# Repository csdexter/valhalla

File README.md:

# Valhalla

This repository contains version-controlled material related to operation
Valhalla. The documentation counterparts are currently stored in Google Drive.

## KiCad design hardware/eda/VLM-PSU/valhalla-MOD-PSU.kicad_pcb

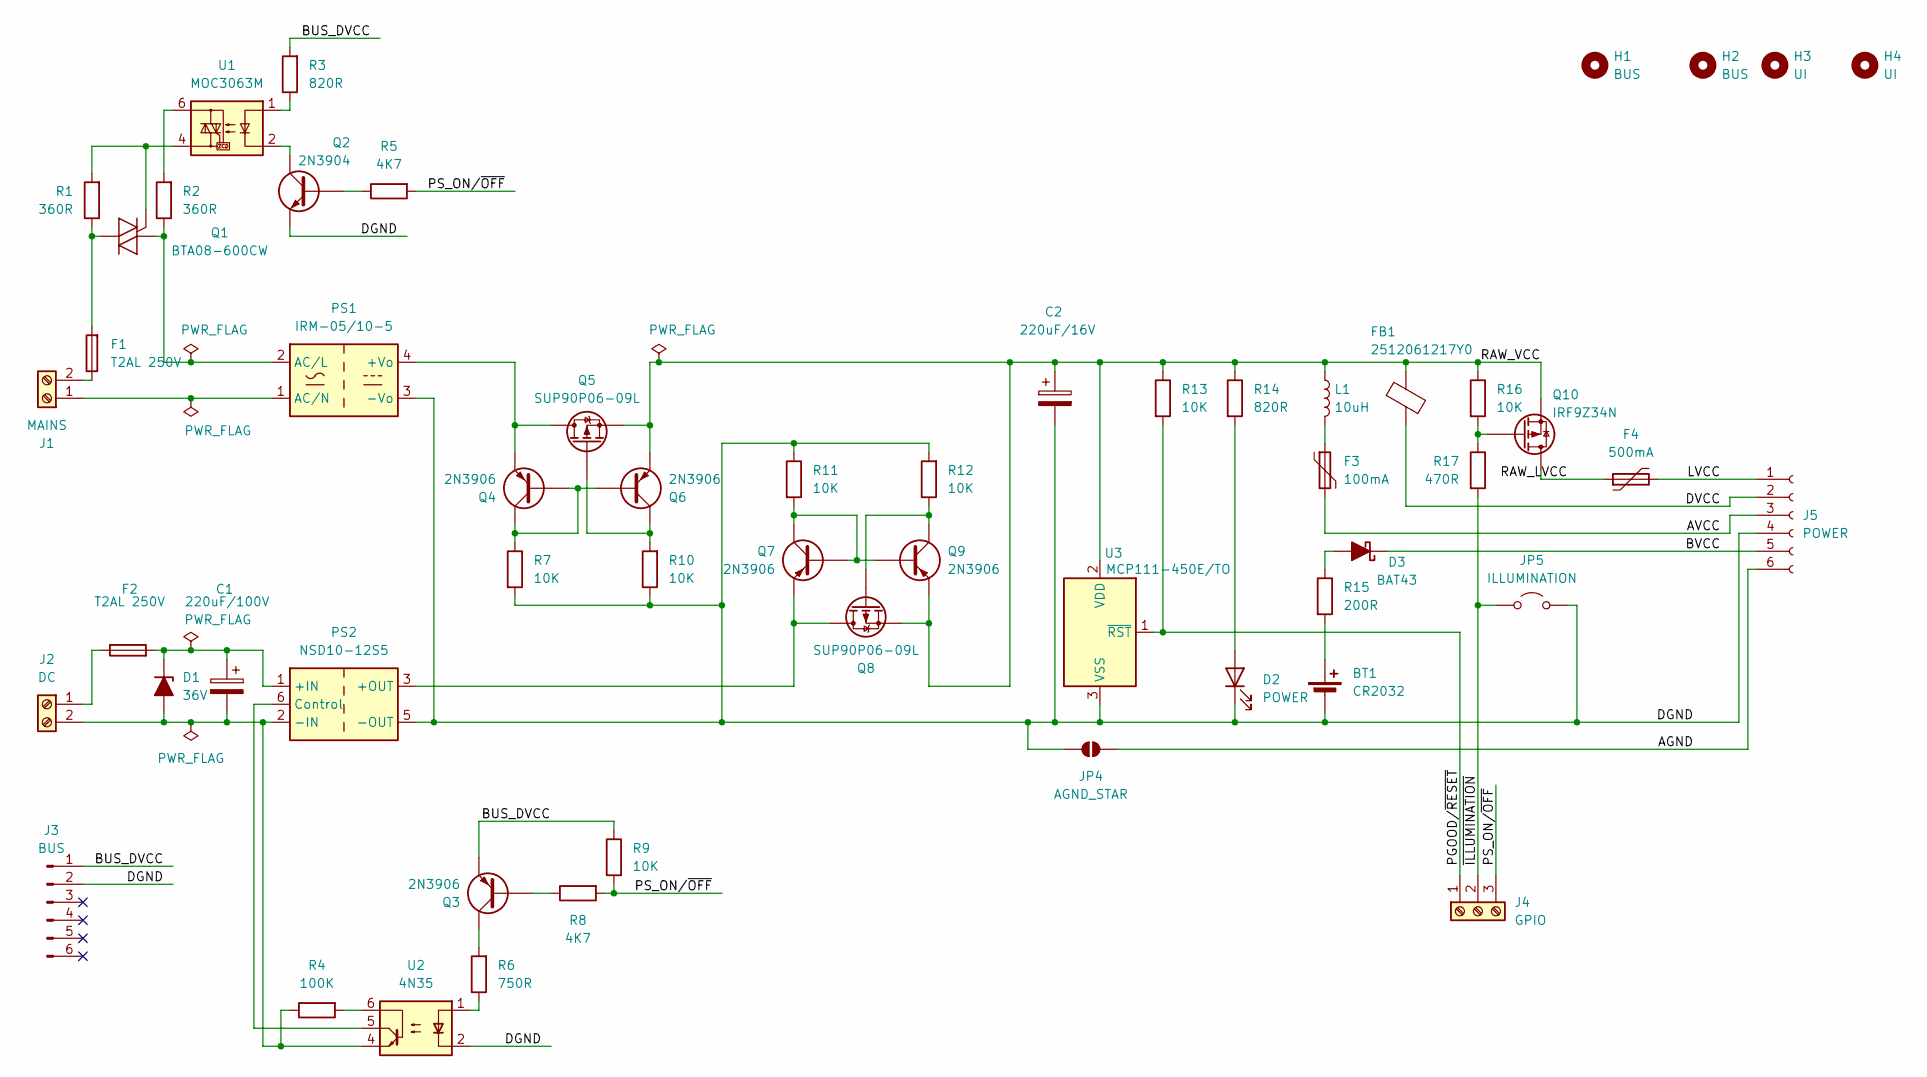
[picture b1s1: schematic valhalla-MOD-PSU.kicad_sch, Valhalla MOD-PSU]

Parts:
BT1: CR2032; BAT-TH_BS-02-A1AJ010
C1: 220uF/100V; CP_Radial_D6.3mm_P2.50mm
C2: 220uF/16V; CP_Radial_D6.3mm_P2.50mm
D1: 36V; D_DO-41_SOD81_P5.08mm_Vertical_KathodeUp
D2: POWER; LED_D3.0mm_Horizontal_O1.27mm_Z2.0mm
D3: BAT43; D_DO-34_SOD68_P5.08mm_Vertical_KathodeUp
F1, F2: T2AL 250V; Fuseholder_Clip-5x20mm_Bel_FC-203-22_Lateral_P17.80x5.00mm_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
F3: 100mA; Fuse_BelFuse_0ZRE0005FF_L8.3mm_W3.8mm
F4: 500mA; Fuse_BelFuse_0ZRE0005FF_L8.3mm_W3.8mm
FB1: 2512061217Y0; L_Axial_L5.0mm_D3.6mm_P10.00mm_Horizontal_Murata_BL01RN1A2A2
H1, H2: BUS; MountingHole_3.2mm_M3_ISO7380
H3, H4: UI; MountingHole_3.2mm_M3_ISO7380
J1: MAINS; TerminalBlock_Phoenix_MKDS-3-2-5.08_1x02_P5.08mm_Horizontal
J2: DC; TerminalBlock_Phoenix_MKDS-3-2-5.08_1x02_P5.08mm_Horizontal
J3: BUS; Molex_KK-254_A-7478-06A_1x06_P2.54mm_Horizontal
J4: GPIO; TerminalBlock_Phoenix_MPT-0,5-3-2.54_1x03_P2.54mm_Horizontal
J5: POWER; CONN-TN_39301060
JP4: AGND_STAR; SolderJumper-2_P1.3mm_Open_RoundedPad1.0x1.5mm
JP5: ILLUMINATION; PinHeader_1x02_P2.54mm_Vertical
L1: 10uH; L_Radial_D8.7mm_P5.00mm_Fastron_07HCP
PS1: IRM-05/10-5; Converter_ACDC_MeanWell_IRM-05-xx_THT
PS2: NSD10-12S5; Converter_DCDC_MeanWell_NSD10_THT
Q1: BTA08-600CW; TO-220-3_Horizontal_TabDown
Q2: 2N3904; TO-92_Wide
Q3, Q4, Q6, Q7, Q9: 2N3906; TO-92_Wide
Q5, Q8: SUP90P06-09L; TO-220-3_Horizontal_TabDown
Q10: IRF9Z34N; TO-220-3_Horizontal_TabDown
R1, R2: 360R; R_Axial_DIN0207_L6.3mm_D2.5mm_P5.08mm_Vertical
R3, R14: 820R; R_Axial_DIN0207_L6.3mm_D2.5mm_P5.08mm_Vertical
R4: 100K; R_Axial_DIN0207_L6.3mm_D2.5mm_P5.08mm_Vertical
R5, R8: 4K7; R_Axial_DIN0207_L6.3mm_D2.5mm_P5.08mm_Vertical
R6: 750R; R_Axial_DIN0207_L6.3mm_D2.5mm_P5.08mm_Vertical
R7, R9, R10, R11, R12, R13, R16: 10K; R_Axial_DIN0207_L6.3mm_D2.5mm_P5.08mm_Vertical
R15: 200R; R_Axial_DIN0207_L6.3mm_D2.5mm_P5.08mm_Vertical
R17: 470R; R_Axial_DIN0207_L6.3mm_D2.5mm_P5.08mm_Vertical
U1: MOC3063M; DIP-6_W10.16mm
U2: 4N35; DIP-6_W7.62mm
U3: MCP111-450E/TO; TO-92_Wide

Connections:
/AGND: J5.6, JP4.2 (B)
/AVCC: F3.2, J5.3
/BUS_DVCC: J3.1, Q3.1 (E), R3.2, R9.1
/BVCC: D3.1 (K), J5.5
/DGND: BT1.2 (-), C2.2, D2.1 (K), J3.2, J5.4, JP4.1 (A), JP5.2 (B), PS1.3 (-Vo), PS2.5 (-OUT), Q2.1 (E), R7.2, R10.1, R11.1, R12.2, U2.2, U3.3 (VSS)
/DVCC: FB1.2, J5.2
/LVCC: F4.2, J5.1
/PGOOD/~RESET: J4.1, R13.2, U3.1 (~RST)
/PS_ON/~OFF: J4.3, R5.2, R8.2, R9.2
/RAW_LVCC: F4.1, Q10.2 (D)
/RAW_VCC: C2.1, FB1.1, L1.1, Q5.3 (S), Q6.1 (E), Q8.3 (S), Q9.1 (E), Q10.3 (S), R13.1, R14.1, R16.1, U3.2 (VDD)
/~ILLUMINATION: J4.2, JP5.1 (A), R17.2
unnamed: BT1.1 (+), R15.2
unnamed: C1.2, D1.2 (A), J2.2, PS2.2 (-IN), R4.1, U2.4
unnamed: C1.1, D1.1 (K), F2.2, PS2.1 (+IN)
unnamed: D2.2 (A), R14.2
unnamed: D3.2 (A), R15.1
unnamed: F3.1, L1.2
unnamed: J1.1, PS1.1 (AC/N)
unnamed: F1.1, J1.2
unnamed: F2.1, J2.1
unnamed: PS1.4 (+Vo), Q4.1 (E), Q5.2 (D)
unnamed: PS1.2 (AC/L), Q1.1 (A1), R2.1
unnamed: PS2.3 (+OUT), Q7.1 (E), Q8.2 (D)
unnamed: PS2.6 (Control), U2.5
unnamed: F1.2, Q1.2 (A2), R1.1
unnamed: Q1.3 (G), R1.2, U1.4
unnamed: Q2.2 (B), R5.1
unnamed: Q2.3 (C), U1.2
unnamed: Q3.2 (B), R8.1
unnamed: Q3.3 (C), R6.2
unnamed: Q4.2 (B), Q4.3 (C), Q6.2 (B), R7.1
unnamed: Q5.1 (G), Q6.3 (C), R10.2
unnamed: Q7.2 (B), Q7.3 (C), Q9.2 (B), R11.2
unnamed: Q8.1 (G), Q9.3 (C), R12.1
unnamed: Q10.1 (G), R16.2, R17.1
unnamed: R2.2, U1.6
unnamed: R3.1, U1.1
unnamed: R4.2, U2.6
unnamed: R6.1, U2.1

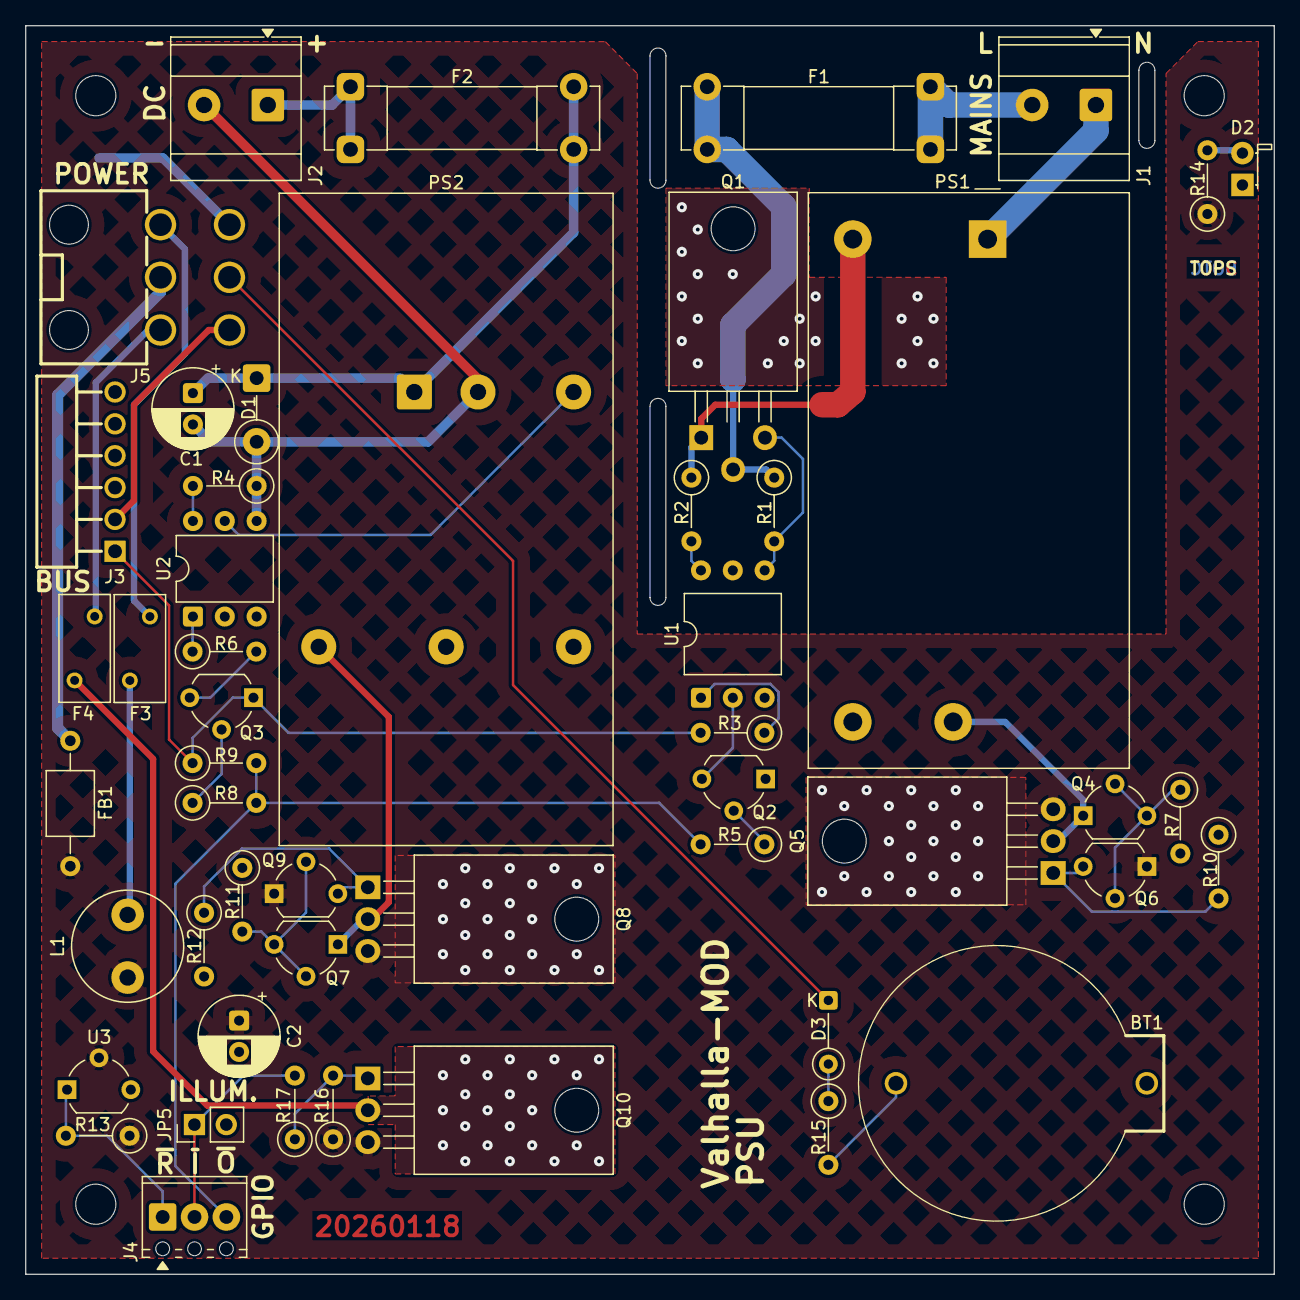
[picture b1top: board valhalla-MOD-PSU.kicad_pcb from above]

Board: 2 copper layers, 99.6 x 99.6 mm, 55 parts (1 on the bottom side), 40 nets.

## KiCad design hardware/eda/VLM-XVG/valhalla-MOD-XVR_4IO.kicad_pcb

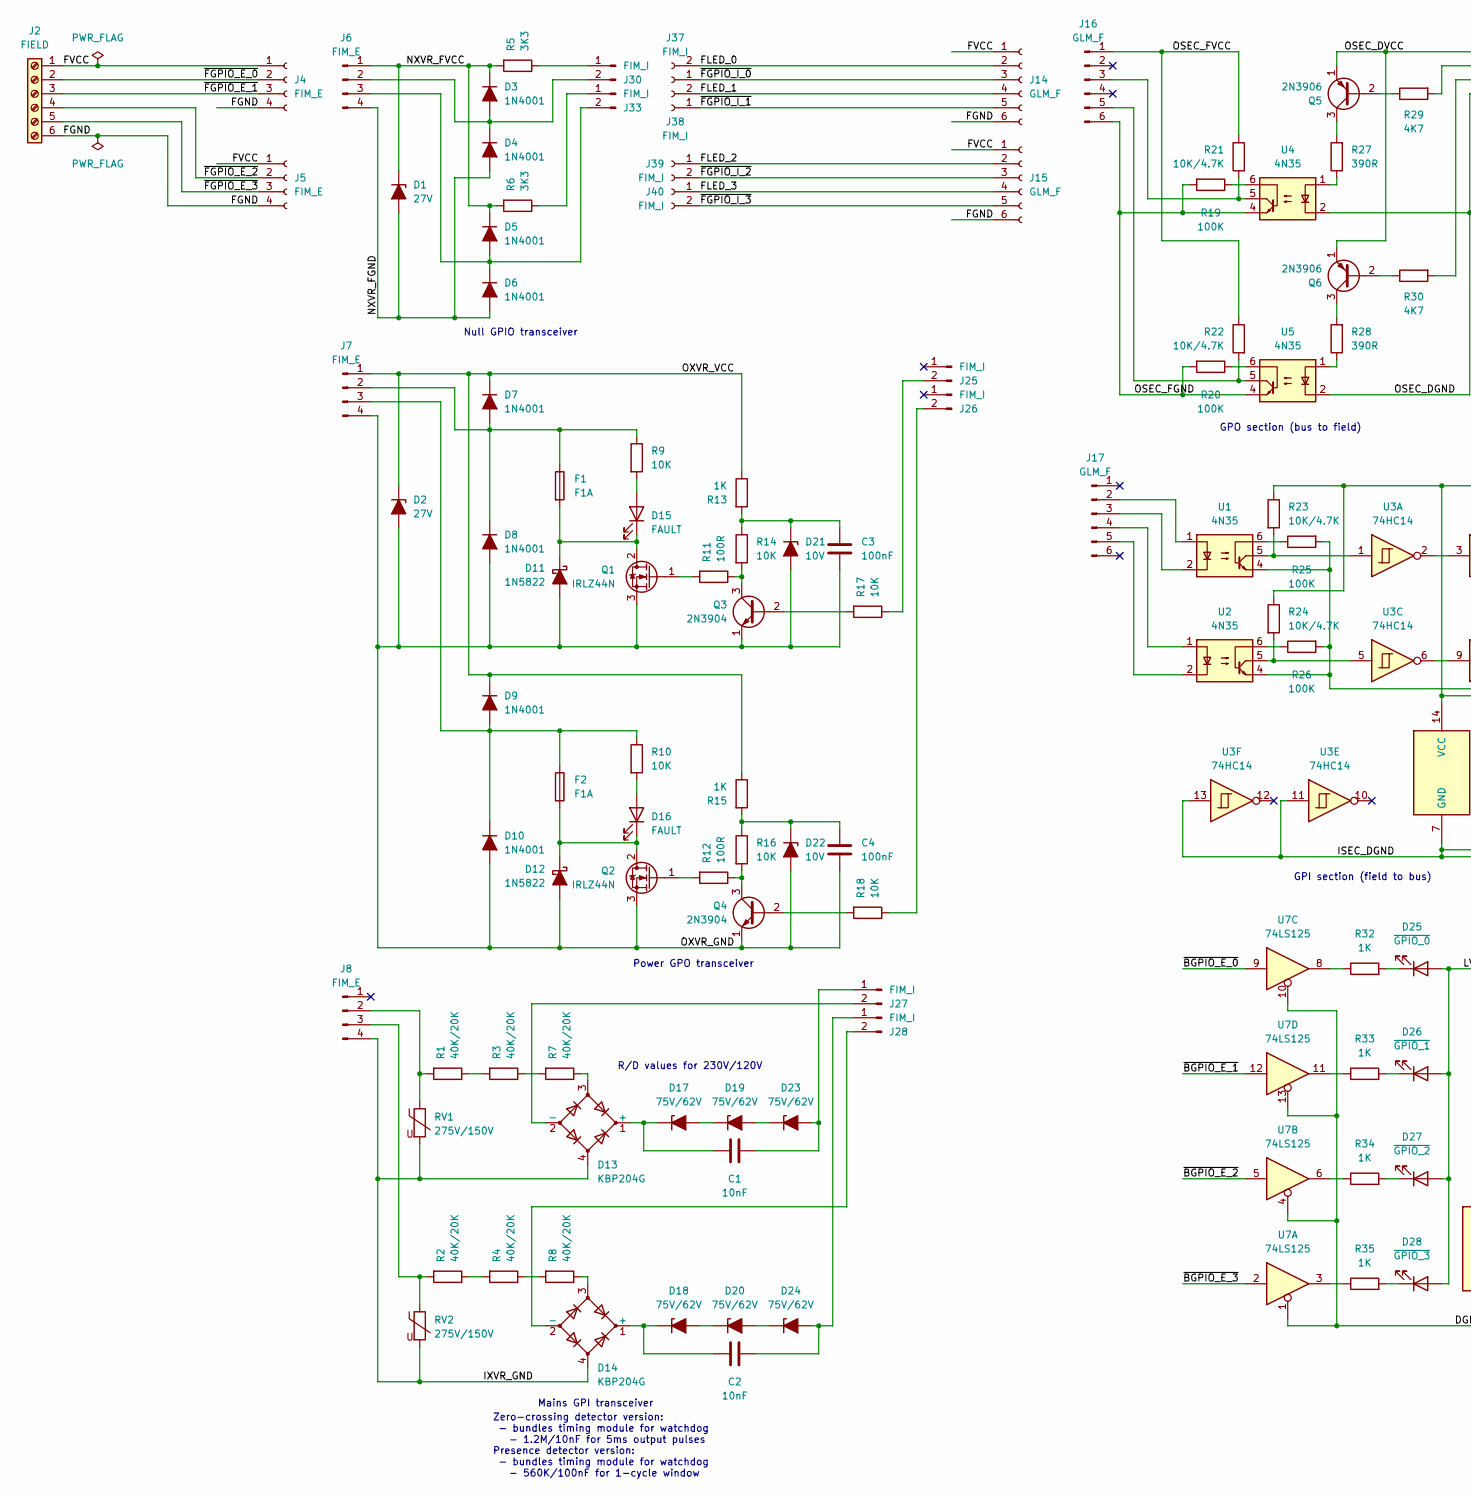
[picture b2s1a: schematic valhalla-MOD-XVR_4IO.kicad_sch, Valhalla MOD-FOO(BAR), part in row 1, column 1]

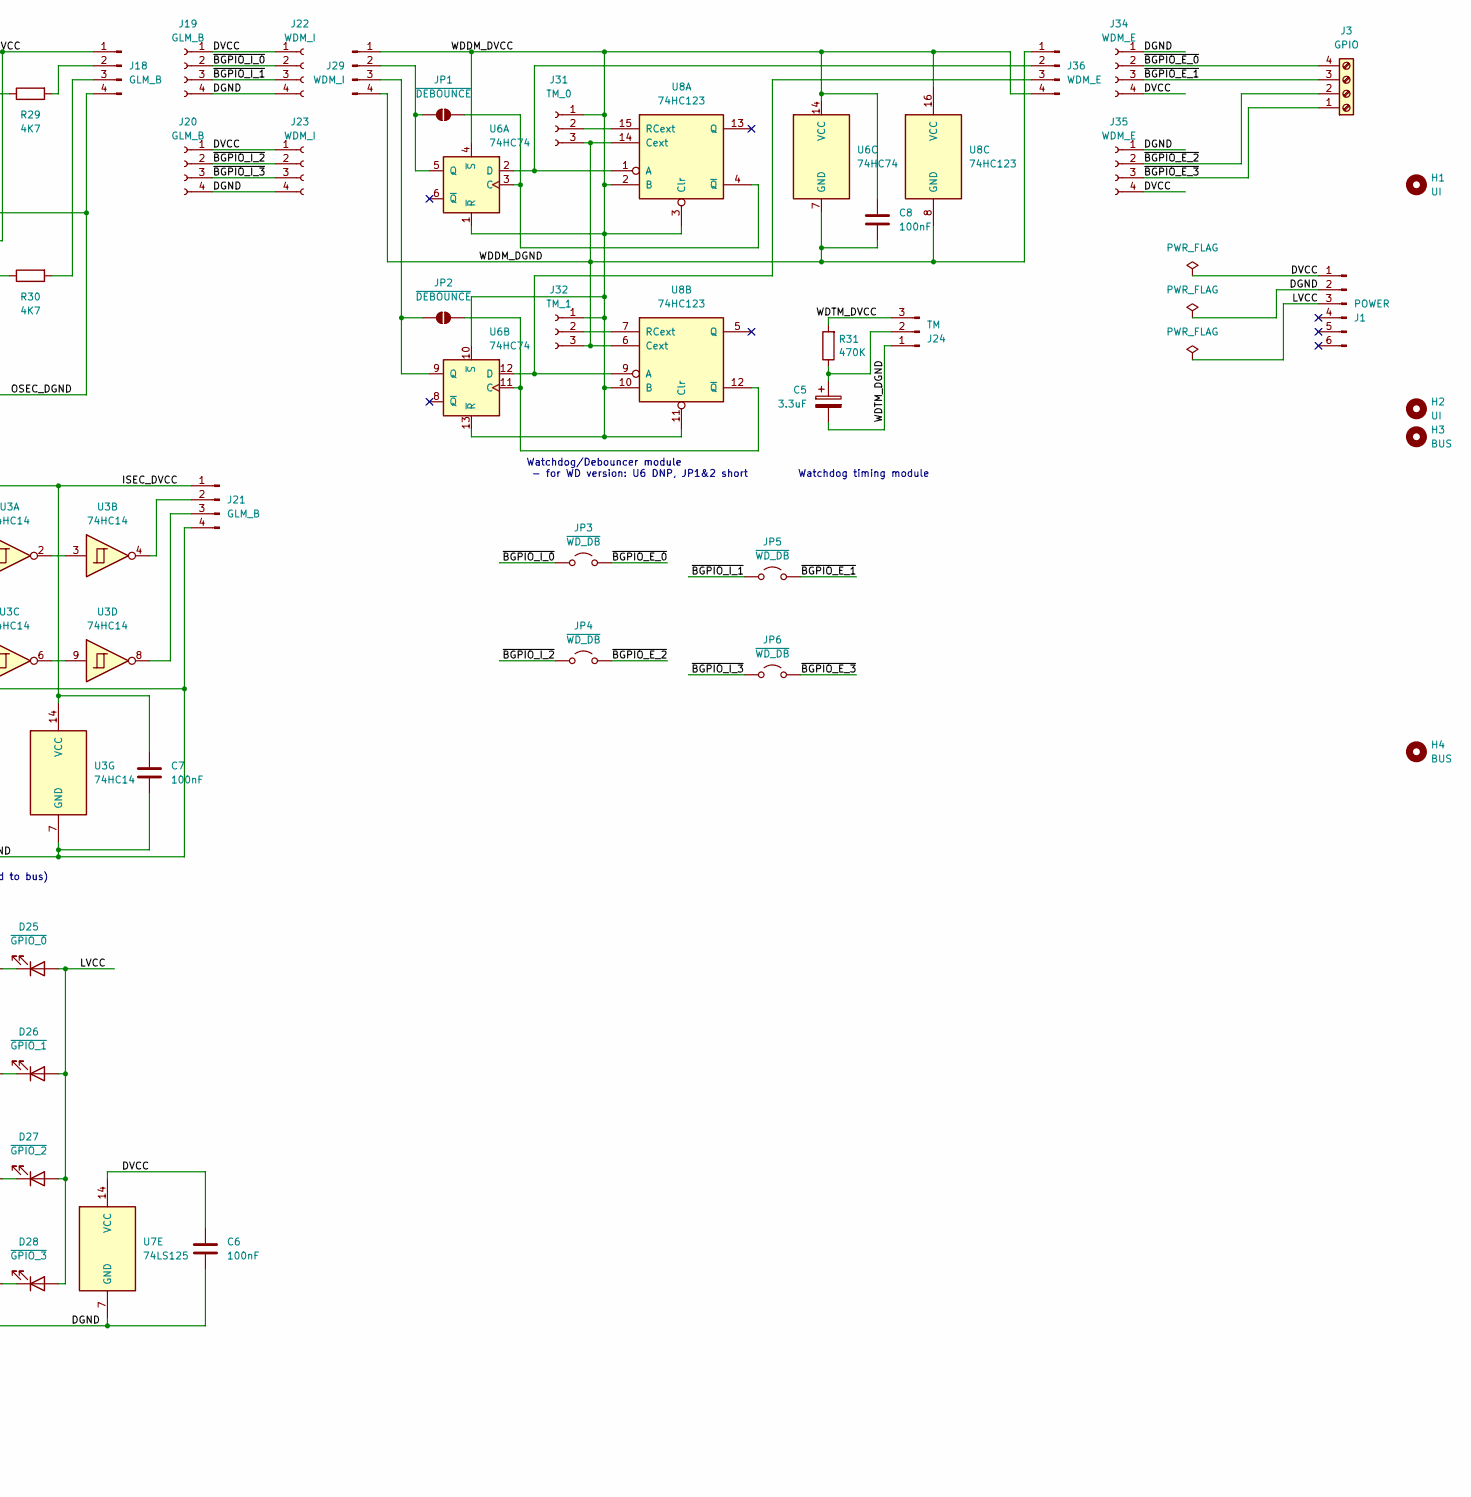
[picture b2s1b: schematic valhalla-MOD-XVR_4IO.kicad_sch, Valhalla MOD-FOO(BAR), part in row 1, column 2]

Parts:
C1, C2: 10nF; C_Disc_D11.0mm_W5.0mm_P7.50mm
C3, C4: 100nF; C_Rect_L7.2mm_W2.5mm_P5.00mm_FKS2_FKP2_MKS2_MKP2
C5: 3.3uF; CP_Radial_D5.0mm_P2.00mm
C6, C7, C8: 100nF; C_Rect_L4.0mm_W2.5mm_P2.50mm
D1, D2: 27V; D_DO-41_SOD81_P5.08mm_Vertical_KathodeUp
D3, D4, D5, D6, D7, D8, D9, D10: 1N4001; D_DO-41_SOD81_P5.08mm_Vertical_KathodeUp
D11, D12: 1N5822; D_DO-201AD_P5.08mm_Vertical_KathodeUp
D13, D14: KBP204G; Diode_Bridge_KBP_14.5x3.5x10.0mm_P3.81mm
D15, D16: FAULT; LED_D3.0mm
D17, D18, D19, D20, D23, D24: 75V/62V; D_DO-41_SOD81_P5.08mm_Vertical_KathodeUp
D21, D22: 10V; D_DO-35_SOD27_P5.08mm_Vertical_KathodeUp
D25: ~{GPIO_0}; LED_D3.0mm_Horizontal_O1.27mm_Z2.0mm
D26: ~{GPIO_1}; LED_D3.0mm_Horizontal_O3.81mm_Z6.0mm
D27: ~{GPIO_2}; LED_D3.0mm_Horizontal_O1.27mm_Z2.0mm
D28: ~{GPIO_3}; LED_D3.0mm_Horizontal_O3.81mm_Z6.0mm
F1, F2: F1A; Fuseholder_Clip-5x20mm_Bel_FC-203-22_Lateral_P17.80x5.00mm_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
H1, H2: UI; MountingHole_3.2mm_M3_ISO7380
H3, H4: BUS; MountingHole_3.2mm_M3_ISO7380
J1: POWER; Molex_KK-254_A-7478-06A_1x06_P2.54mm_Horizontal
J2: FIELD; TerminalBlock_Phoenix_MKDS-3-6-5.08_1x06_P5.08mm_Horizontal
J3: GPIO; TerminalBlock_Phoenix_MPT-0,5-4-2.54_1x04_P2.54mm_Horizontal
J4, J5: FIM_E; PinSocket_1x04_P2.54mm_Vertical
J6, J7, J8: FIM_E; PinHeader_1x04_P2.54mm_Vertical
J14, J15: GLM_F; PinSocket_1x06_P2.54mm_Vertical
J16, J17: GLM_F; PinHeader_1x06_P2.54mm_Vertical
J18, J21: GLM_B; PinHeader_1x04_P2.54mm_Vertical
J19, J20: GLM_B; PinSocket_1x04_P2.54mm_Vertical
J22, J23: WDM_I; PinSocket_1x04_P2.54mm_Vertical
J24: TM; PinHeader_1x03_P2.54mm_Horizontal
J25, J26, J27, J28, J30, J33: FIM_I; PinHeader_1x02_P2.54mm_Vertical
J29: WDM_I; PinHeader_1x04_P2.54mm_Vertical
J31: TM_0; PinSocket_1x03_P2.54mm_Horizontal
J32: TM_1; PinSocket_1x03_P2.54mm_Horizontal
J34, J35: WDM_E; PinSocket_1x04_P2.54mm_Vertical
J36: WDM_E; PinHeader_1x04_P2.54mm_Vertical
J37, J38, J39, J40: FIM_I; PinSocket_1x02_P2.54mm_Vertical
JP1, JP2: ~{DEBOUNCE}; SolderJumper-2_P1.3mm_Open_TrianglePad1.0x1.5mm
JP3, JP4, JP5, JP6: ~{WD_DB}; PinHeader_1x02_P2.54mm_Vertical
Q1, Q2: IRLZ44N; TO-220-3_Vertical
Q3, Q4: 2N3904; TO-92_Wide
Q5, Q6: 2N3906; TO-92_Wide
R1, R2, R3, R4, R7, R8: 40K/20K; R_Axial_DIN0207_L6.3mm_D2.5mm_P5.08mm_Vertical
R5, R6: 3K3; R_Axial_DIN0207_L6.3mm_D2.5mm_P5.08mm_Vertical
R9, R10, R14, R16, R17, R18: 10K; R_Axial_DIN0207_L6.3mm_D2.5mm_P5.08mm_Vertical
R11, R12: 100R; R_Axial_DIN0207_L6.3mm_D2.5mm_P5.08mm_Vertical
R13, R15, R32, R33, R34, R35: 1K; R_Axial_DIN0207_L6.3mm_D2.5mm_P5.08mm_Vertical
R19, R20, R25, R26: 100K; R_Axial_DIN0207_L6.3mm_D2.5mm_P5.08mm_Vertical
R21, R22, R23, R24: 10K/4.7K; R_Axial_DIN0207_L6.3mm_D2.5mm_P5.08mm_Vertical
R27, R28: 390R; R_Axial_DIN0207_L6.3mm_D2.5mm_P5.08mm_Vertical
R29, R30: 4K7; R_Axial_DIN0207_L6.3mm_D2.5mm_P5.08mm_Vertical
R31: 470K; R_Axial_DIN0207_L6.3mm_D2.5mm_P10.16mm_Horizontal
RV1, RV2: 275V/150V; RV_Disc_D7mm_W3.4mm_P5mm
U1, U2, U4, U5: 4N35; DIP-6_W7.62mm
U3: 74HC14; DIP-14_W7.62mm
U6: 74HC74; DIP-14_W7.62mm
U7: 74LS125; DIP-14_W7.62mm
U8: 74HC123; DIP-16_W7.62mm

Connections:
/DGND: C6.2, J1.2, J19.4, J20.4, J22.4, J23.4, J34.1, J35.1, U7.1, U7.4, U7.7 (GND), U7.10, U7.13
/DVCC: C6.1, J1.1, J19.1, J20.1, J22.1, J23.1, J34.4, J35.4, U7.14 (VCC)
/FGND: J2.6, J4.4, J5.4, J14.6, J15.6
/FLED_0: J14.2, J37.2
/FLED_1: J14.4, J38.2
/FLED_2: J15.2, J39.1
/FLED_3: J15.4, J40.1
/FVCC: J2.1, J4.1, J5.1, J14.1, J15.1
/ISEC_DGND: C7.2, J21.4, R25.2, R26.2, U1.4, U2.4, U3.7 (GND), U3.11, U3.13
/ISEC_DVCC: C7.1, J21.1, R23.1, R24.1, U3.14 (VCC)
/IXVR_GND: D13.4, D14.4, J8.4, RV1.2, RV2.2
/LVCC: D25.2 (A), D26.2 (A), D27.2 (A), D28.2 (A), J1.3
/NXVR_FGND: D1.2 (A), D4.2 (A), D6.2 (A), J6.4
/NXVR_FVCC: D1.1 (K), D3.1 (K), D5.1 (K), J6.1, R5.2, R6.2
/OSEC_DGND: J18.4, U4.2, U5.2
/OSEC_DVCC: J18.1, Q5.1 (E), Q6.1 (E)
/OSEC_FGND: J16.6, R19.2, R20.2, U4.4, U5.4
/OSEC_FVCC: J16.1, R21.1, R22.1
/OXVR_GND: C3.2, C4.2, D2.2 (A), D8.2 (A), D10.2 (A), D11.2 (A), D12.2 (A), D21.2 (A), D22.2 (A), J7.4, Q1.3 (S), Q2.3 (S), Q3.1 (E), Q4.1 (E)
/OXVR_VCC: D2.1 (K), D7.1 (K), D9.1 (K), J7.1, R13.1, R15.1
/WDDM_DGND: C8.2, J29.4, J31.3, J32.3, J36.1, U6.7 (GND), U8.6 (Cext), U8.8 (GND), U8.14 (Cext)
/WDDM_DVCC: C8.1, J29.1, J31.1, J32.1, J36.4, U6.1 (~R), U6.4 (~S), U6.10 (~S), U6.13 (~R), U6.14 (VCC), U8.2 (B), U8.3 (Clr), U8.10 (B), U8.11 (Clr), U8.16 (VCC)
/WDTM_DGND: C5.2, J24.1
/WDTM_DVCC: J24.3, R31.2
/~BGPIO_E_0: J3.4, J34.2, JP3.2 (B), U7.9
/~BGPIO_E_1: J3.3, J34.3, JP5.2 (B), U7.12
/~BGPIO_E_2: J3.2, J35.2, JP4.2 (B), U7.5
/~BGPIO_E_3: J3.1, J35.3, JP6.2 (B), U7.2
/~BGPIO_I_0: J19.2, J22.2, JP3.1 (A)
/~BGPIO_I_1: J19.3, J22.3, JP5.1 (A)
/~BGPIO_I_2: J20.2, J23.2, JP4.1 (A)
/~BGPIO_I_3: J20.3, J23.3, JP6.1 (A)
/~FGPIO_E_0: J2.2, J4.2
/~FGPIO_E_1: J2.3, J4.3
/~FGPIO_E_2: J2.4, J5.2
/~FGPIO_E_3: J2.5, J5.3
/~FGPIO_I_0: J14.3, J37.1
/~FGPIO_I_1: J14.5, J38.1
/~FGPIO_I_2: J15.3, J39.2
/~FGPIO_I_3: J15.5, J40.2
unnamed: D3.2 (A), D4.1 (K), J6.2, J30.2
unnamed: D5.2 (A), D6.1 (K), J6.3, J33.2
unnamed: D7.2 (A), D8.1 (K), F1.1, J7.2, R9.1
unnamed: D9.2 (A), D10.1 (K), F2.1, J7.3, R10.1
unnamed: D11.1 (K), D15.1 (K), F1.2, Q1.2 (D)
unnamed: D12.1 (K), D16.1 (K), F2.2, Q2.2 (D)
unnamed: C1.1, D13.1 (+), D17.1 (K)
unnamed: D13.2 (-), J27.2
unnamed: D13.3, R7.1
unnamed: C2.1, D14.1 (+), D18.1 (K)
unnamed: D14.2 (-), J28.2
unnamed: D14.3, R8.1
unnamed: D15.2 (A), R9.2
unnamed: D16.2 (A), R10.2
unnamed: D17.2 (A), D19.1 (K)
unnamed: D18.2 (A), D20.1 (K)
unnamed: D19.2 (A), D23.1 (K)
unnamed: D20.2 (A), D24.1 (K)
unnamed: C3.1, D21.1 (K), R13.2, R14.1
unnamed: C4.1, D22.1 (K), R15.2, R16.1
unnamed: C1.2, D23.2 (A), J27.1
unnamed: C2.2, D24.2 (A), J28.1
unnamed: D25.1 (K), R32.2
unnamed: D26.1 (K), R33.2
unnamed: D27.1 (K), R34.2
unnamed: D28.1 (K), R35.2
unnamed: J8.2, R1.2, RV1.1
unnamed: J8.3, R2.2, RV2.1
unnamed: J16.3, R21.2, U4.5
unnamed: J16.5, R22.2, U5.5
unnamed: J17.2, U1.1
unnamed: J17.3, U1.2
unnamed: J17.4, U2.1
unnamed: J17.5, U2.2
unnamed: J18.2, R29.2
unnamed: J18.3, R30.2
unnamed: J21.2, U3.4
unnamed: J21.3, U3.8
unnamed: C5.1, J24.2, R31.1
unnamed: J25.2, R17.1
unnamed: J26.2, R18.1
unnamed: J29.2, JP1.1 (A), U6.5 (Q)
unnamed: J29.3, JP2.1 (A), U6.9 (Q)
unnamed: J30.1, R5.1
unnamed: J31.2, U8.15 (RCext)
unnamed: J32.2, U8.7 (RCext)
unnamed: J33.1, R6.1
unnamed: J36.2, U6.2 (D), U8.1 (A)
unnamed: J36.3, U6.12 (D), U8.9 (A)
unnamed: JP1.2 (B), U6.3 (C), U8.4 (~Q)
unnamed: JP2.2 (B), U6.11 (C), U8.12 (~Q)
unnamed: Q1.1 (G), R11.2
unnamed: Q2.1 (G), R12.2
unnamed: Q3.2 (B), R17.2
unnamed: Q3.3 (C), R11.1, R14.2
unnamed: Q4.2 (B), R18.2
unnamed: Q4.3 (C), R12.1, R16.2
unnamed: Q5.2 (B), R29.1
unnamed: Q5.3 (C), R27.2
unnamed: Q6.2 (B), R30.1
unnamed: Q6.3 (C), R28.2
unnamed: R1.1, R3.2
unnamed: R2.1, R4.2
unnamed: R3.1, R7.2
unnamed: R4.1, R8.2
unnamed: R19.1, U4.6
unnamed: R20.1, U5.6
unnamed: R23.2, U1.5, U3.1
unnamed: R24.2, U2.5, U3.5
unnamed: R25.1, U1.6
unnamed: R26.1, U2.6
unnamed: R27.1, U4.1
unnamed: R28.1, U5.1
unnamed: R32.1, U7.8
unnamed: R33.1, U7.11
unnamed: R34.1, U7.6
unnamed: R35.1, U7.3
unnamed: U3.2, U3.3
unnamed: U3.6, U3.9

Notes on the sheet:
Watchdog timing module
GPO section (bus to field)
Mains GPI transceiver
R/D values for 230V/120V
GPI section (field to bus)
Presence detector version: - bundles timing module for watchdog - 560K/100nF for 1-cycle window
Null GPIO transceiver
Power GPO transceiver
Watchdog/Debouncer module - for WD version: U6 DNP, JP1&2 short
Zero-crossing detector version: - bundles timing module for watchdog - 1.2M/10nF for 5ms output pulses

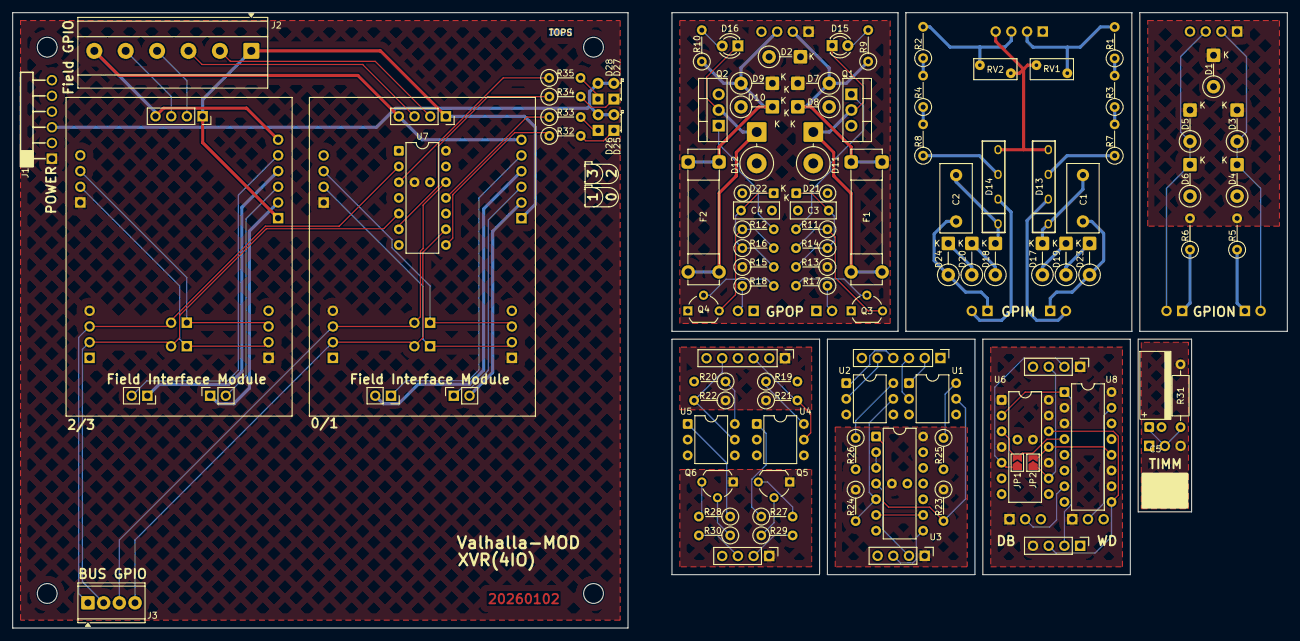
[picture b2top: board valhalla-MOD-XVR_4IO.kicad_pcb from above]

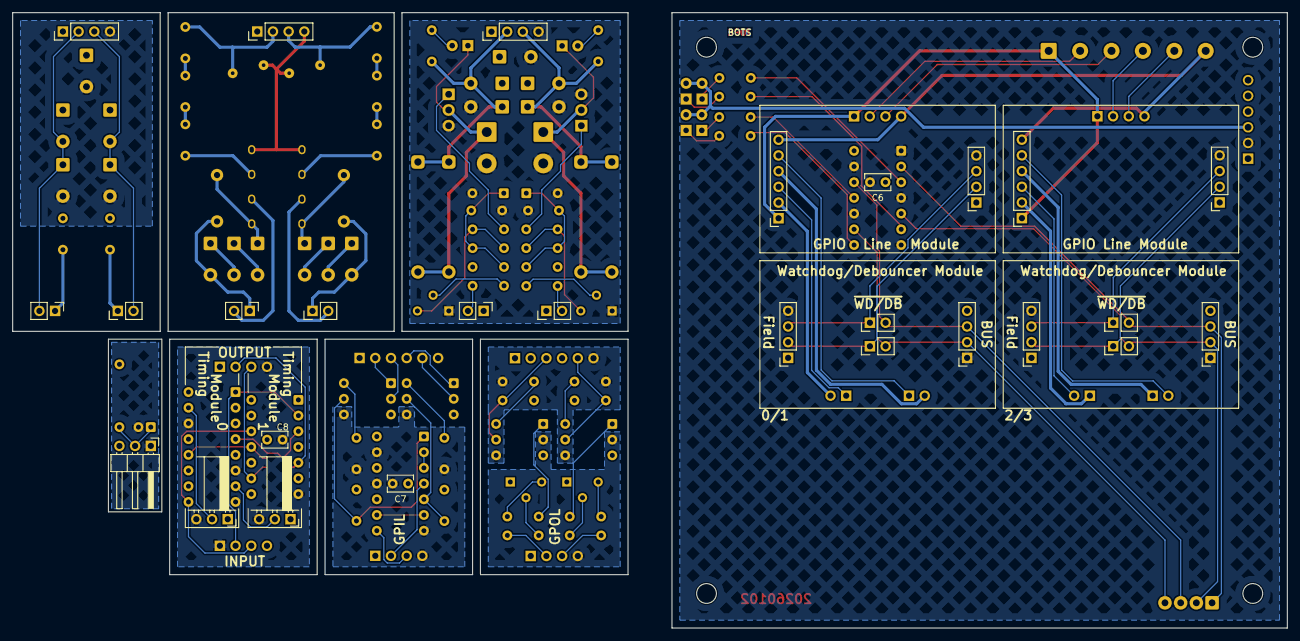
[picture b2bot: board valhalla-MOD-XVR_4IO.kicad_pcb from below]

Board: 2 copper layers, 206.2 x 99.6 mm, 134 parts (27 on the bottom side), 119 nets.

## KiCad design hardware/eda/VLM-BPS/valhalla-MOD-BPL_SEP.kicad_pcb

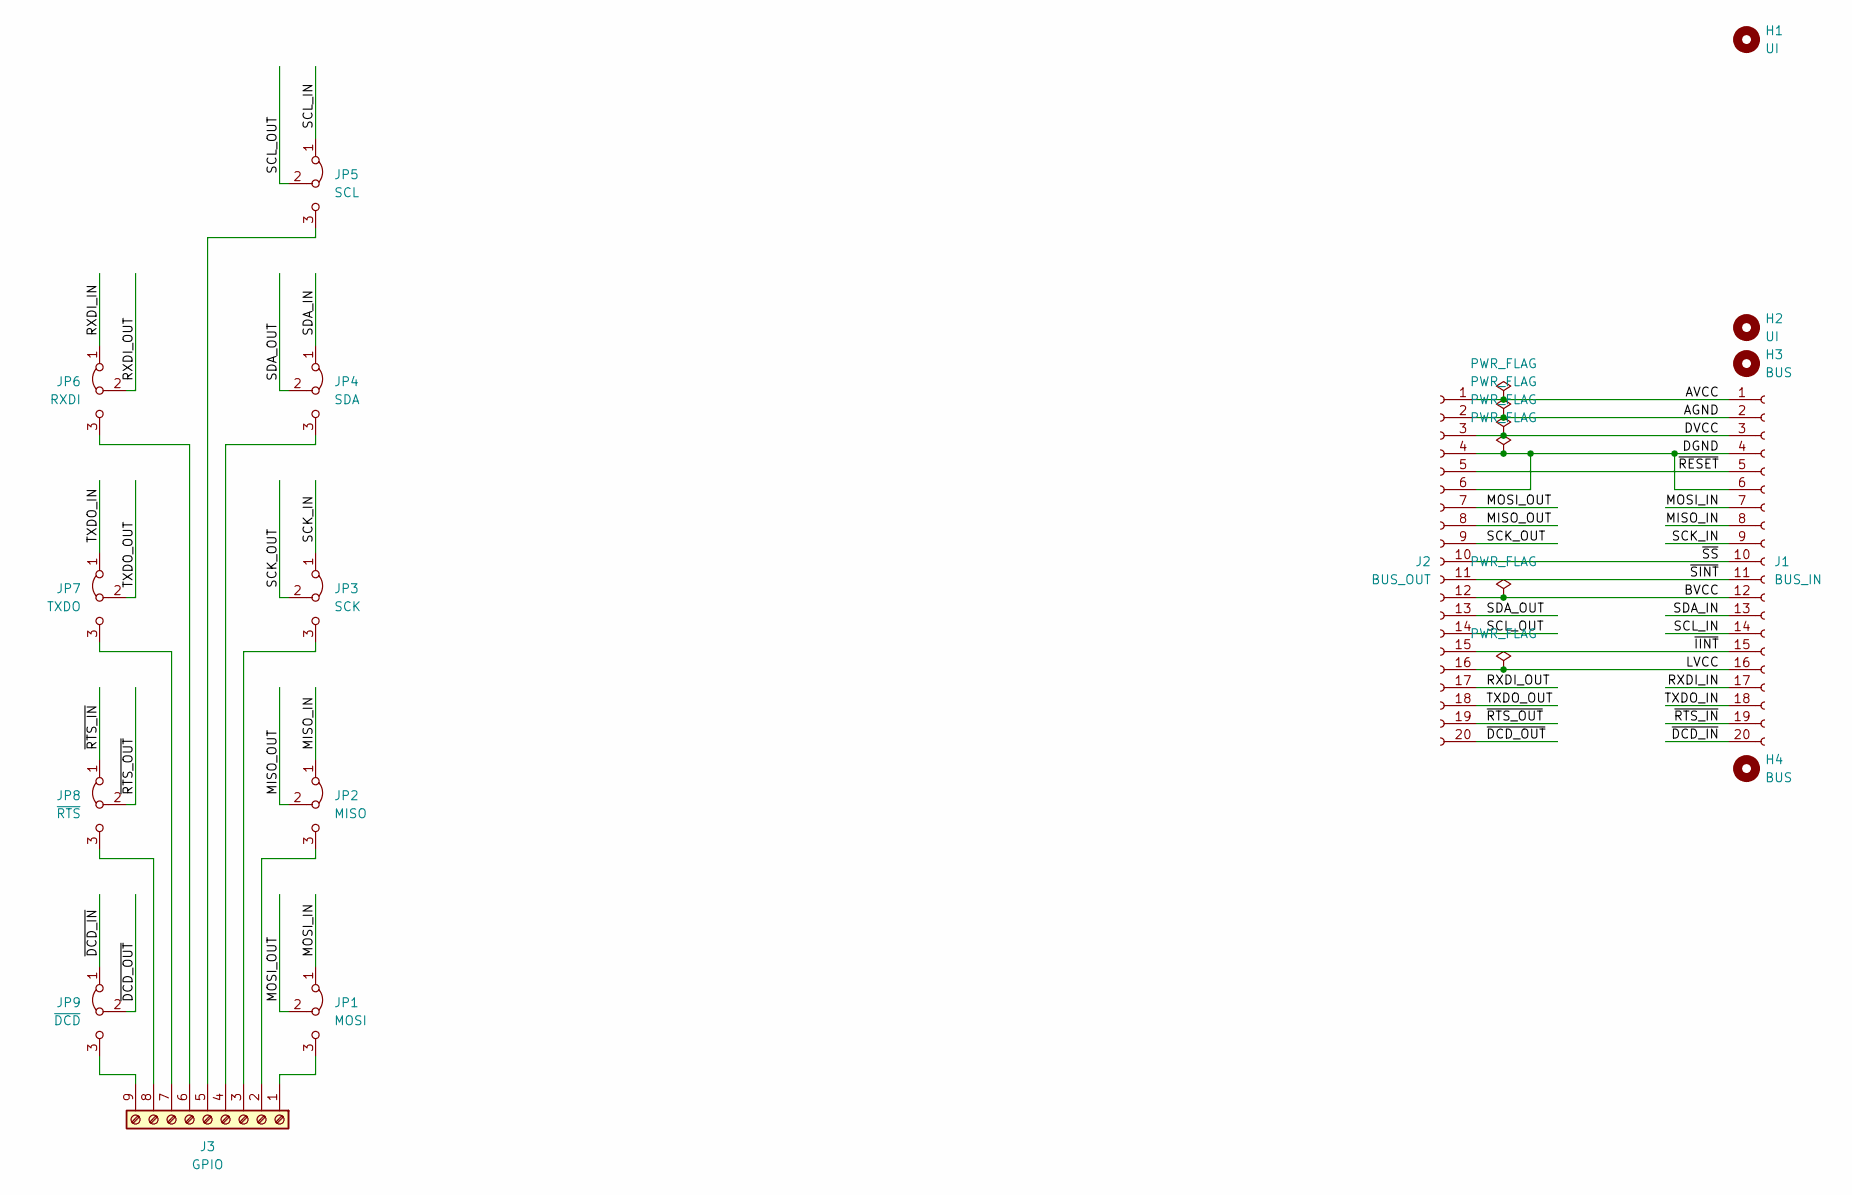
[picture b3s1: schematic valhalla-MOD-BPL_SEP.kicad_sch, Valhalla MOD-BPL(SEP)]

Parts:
H1, H2: UI; MountingHole_3.2mm_M3_ISO7380
H3, H4: BUS; MountingHole_3.2mm_M3_ISO7380
J1: BUS_IN; PinSocket_2x10_P2.54mm_Vertical_SMD
J2: BUS_OUT; PinHeader_2x10_P2.54mm_Vertical_SMD
J3: GPIO; TerminalBlock_Phoenix_MPT-0,5-9-2.54_1x09_P2.54mm_Horizontal
JP1: MOSI; PinHeader_1x03_P2.54mm_Vertical
JP2: MISO; PinHeader_1x03_P2.54mm_Vertical
JP3: SCK; PinHeader_1x03_P2.54mm_Vertical
JP4: SDA; PinHeader_1x03_P2.54mm_Vertical
JP5: SCL; PinHeader_1x03_P2.54mm_Vertical
JP6: RXDI; PinHeader_1x03_P2.54mm_Vertical
JP7: TXDO; PinHeader_1x03_P2.54mm_Vertical
JP8: ~{RTS}; PinHeader_1x03_P2.54mm_Vertical
JP9: ~{DCD}; PinHeader_1x03_P2.54mm_Vertical

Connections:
/AGND: J1.2, J2.2
/AVCC: J1.1, J2.1
/BVCC: J1.12, J2.12
/DGND: J1.4, J1.6, J2.4, J2.6
/DVCC: J1.3, J2.3
/LVCC: J1.16, J2.16
/MISO_IN: J1.8, JP2.1 (A)
/MISO_OUT: J2.8, JP2.2 (C)
/MOSI_IN: J1.7, JP1.1 (A)
/MOSI_OUT: J2.7, JP1.2 (C)
/RXDI_IN: J1.17, JP6.1 (A)
/RXDI_OUT: J2.17, JP6.2 (C)
/SCK_IN: J1.9, JP3.1 (A)
/SCK_OUT: J2.9, JP3.2 (C)
/SCL_IN: J1.14, JP5.1 (A)
/SCL_OUT: J2.14, JP5.2 (C)
/SDA_IN: J1.13, JP4.1 (A)
/SDA_OUT: J2.13, JP4.2 (C)
/TXDO_IN: J1.18, JP7.1 (A)
/TXDO_OUT: J2.18, JP7.2 (C)
/~DCD_IN: J1.20, JP9.1 (A)
/~DCD_OUT: J2.20, JP9.2 (C)
/~IINT: J1.15, J2.15
/~RESET: J1.5, J2.5
/~RTS_IN: J1.19, JP8.1 (A)
/~RTS_OUT: J2.19, JP8.2 (C)
/~SINT: J1.11, J2.11
/~SS: J1.10, J2.10
unnamed: J3.1, JP1.3 (B)
unnamed: J3.2, JP2.3 (B)
unnamed: J3.3, JP3.3 (B)
unnamed: J3.4, JP4.3 (B)
unnamed: J3.5, JP5.3 (B)
unnamed: J3.6, JP6.3 (B)
unnamed: J3.7, JP7.3 (B)
unnamed: J3.8, JP8.3 (B)
unnamed: J3.9, JP9.3 (B)

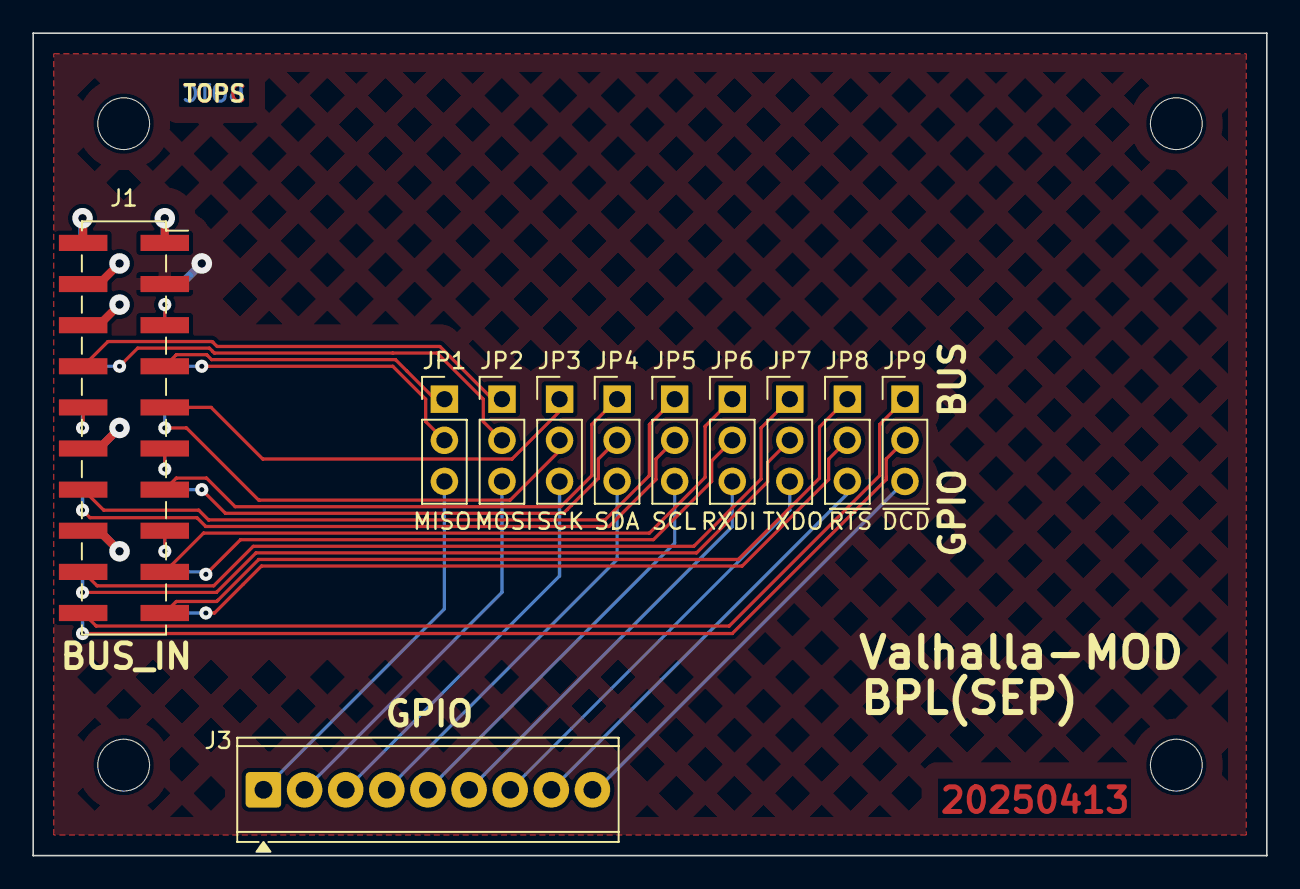
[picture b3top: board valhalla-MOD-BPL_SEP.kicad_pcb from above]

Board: 2 copper layers, 76.2 x 50.8 mm, 16 parts (1 on the bottom side), 37 nets.
